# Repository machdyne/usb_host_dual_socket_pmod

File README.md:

# USB Host Dual Socket Pmod™ Compatible Module

This PMOD is designed for implementing USB host mode directly in an FPGA. It contains the necessary resistors as well as a boost converter to supply 5V to the USB VBUS.

This repo contains PCB layouts, schematics and pinouts.

Find more information on the [product page](https://machdyne.com/product/usb-host-dual-socket-pmod/).

## Pinout

| Pin | Signal |
| --- | ------ |
| 1 | USB2\_DP (bottom socket) |
| 2 | USB2\_DN (bottom socket) |
| 3 | USB1\_DP (top socket) |
| 4 | USB1\_DN (top socket)  |
| 5 | GND |
| 6 | 3V3|
| 7 | NC |
| 8 | NC |
| 9 | NC |
| 10 | NC |
| 11 | GND |
| 12 | 3V3|

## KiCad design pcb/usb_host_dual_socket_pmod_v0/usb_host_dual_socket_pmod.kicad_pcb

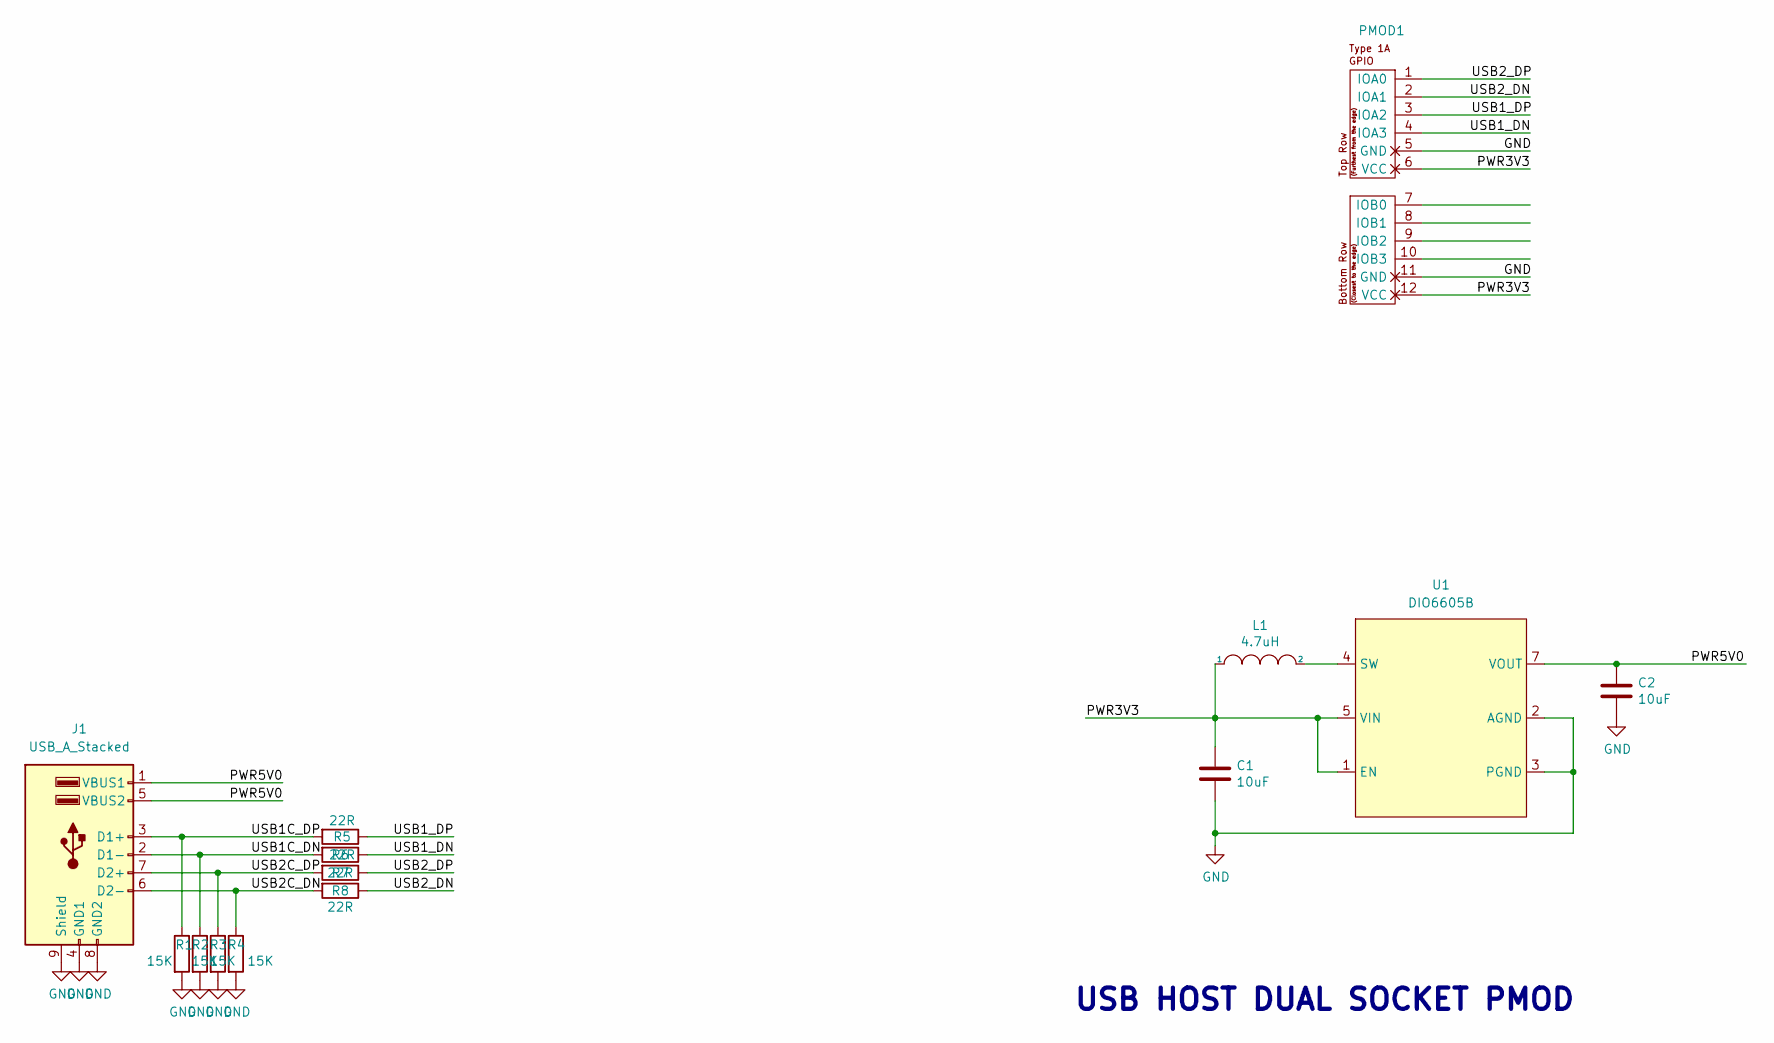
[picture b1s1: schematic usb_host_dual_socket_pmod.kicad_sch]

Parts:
C1, C2: 10uF; L_0603_1608Metric
J1: USB_A_Stacked; USB_A_Wuerth_61400826021_Horizontal_Stacked
L1: 4.7uH; L_0805_2012Metric
PMOD1: PMOD-Device-x2-Type-1A-GPIO; pmod_pin_array_6x2
R1, R2, R3, R4: 15K; R_0402_1005Metric
R5, R6, R7, R8: 22R; R_0402_1005Metric
U1: DIO6605B; TDFN-8-1EP_3x2mm_P0.5mm_EP1.4x1.4mm

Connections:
/PWR3V3: C1.1, L1.1, PMOD1.6 (VCC), PMOD1.12 (VCC), U1.1 (EN), U1.5 (VIN)
/PWR5V0: C2.1, J1.1 (VBUS1), J1.5 (VBUS2), U1.7 (VOUT)
/USB1C_DN: J1.2 (D1-), R2.1, R6.2
/USB1C_DP: J1.3 (D1+), R1.1, R5.2
/USB1_DN: PMOD1.4 (IOA3), R6.1
/USB1_DP: PMOD1.3 (IOA2), R5.1
/USB2C_DN: J1.6 (D2-), R4.1, R8.2
/USB2C_DP: J1.7 (D2+), R3.1, R7.2
/USB2_DN: PMOD1.2 (IOA1), R8.1
/USB2_DP: PMOD1.1 (IOA0), R7.1
GND: C1.2, C2.2, J1.4 (GND1), J1.8 (GND2), J1.9 (Shield), PMOD1.5 (GND), PMOD1.11 (GND), R1.2, R2.2, R3.2, R4.2, U1.2 (AGND), U1.3 (PGND)
unnamed: L1.2, U1.4 (SW)

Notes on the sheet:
USB HOST DUAL SOCKET PMOD

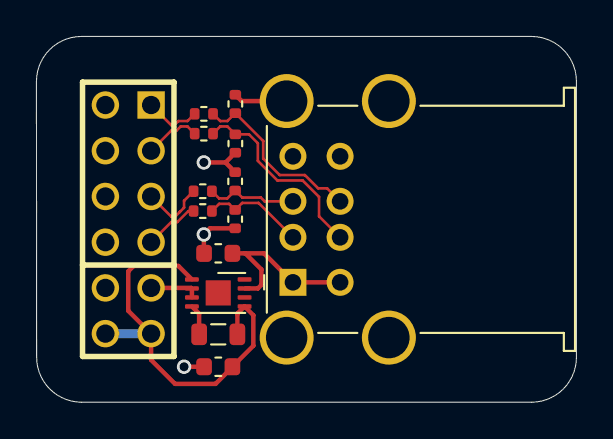
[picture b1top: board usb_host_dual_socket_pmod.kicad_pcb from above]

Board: 2 copper layers, 30.0 x 20.3 mm, 14 parts (0 on the bottom side), 12 nets.

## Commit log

2023-02-09 add image
2023-10-07 add pcb layout

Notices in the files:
pcb/usb_host_dual_socket_pmod_v0/usb_host_dual_socket_pmod.kicad_sch:
Copyright © 2023 Lone Dynamics Corporation
